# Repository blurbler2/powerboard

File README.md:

# Powerboard v1

A small 3.3 V supply module for battery-powered microcontroller projects: 4x AA NiMH in,
regulated 3.3 V out, with an ultra-low quiescent current buck converter (TI TPS62842, 60 nA Iq),
a switchable battery-voltage divider for an MCU ADC, a jumper for current measurement and
test points. Breadboard format with two 1x04 pin headers 12.7 mm apart, like
[olmBoard](https://github.com/azerimaker/olmBoard) (which uses the TPS62840 from the same family).

| | |
|---|---|
| Input | 4x AA NiMH, 4.8 ... 5.6 V (converter accepts 1.8 ... 6.5 V) |
| Output | 3.3 V (set by R7 = 52.3 kΩ 1 %) |
| Output current | up to 750 mA (converter limit); F1 holds 500 mA from the battery, which is about 600 mA at 3.3 V even with nearly empty cells. SW1 carries no load current (see [SW1](#sw1-onoff-switch)) |
| Quiescent current | ON: 60 nA (TPS62842) + MOSFET leakage, the battery divider draws nothing while it is off. OFF: converter shut down, 25 nA typ. (datasheet max 300 nA) + leakage |
| Protection | 500 mA polyfuse F1, reverse-polarity Schottky diode D1 (SS14) |
| Board | 16.0 x 45.72 mm, 2 layers, 1.6 mm, KiCad 10 |

## Board overview

Top view, switch at the top edge:

```
     ON <-- SW1 --> OFF  (actuator sticks out over the edge)
   Q1 R3              D1        F1
   R1 Q2                        J1  (battery: + upper pin, - square pad)
   R2 R4   TP1 (+BATT)
   C17     C14 C15 C2
   TP3 (GND)    U1                  TOP
                L1 R7
  J3 ●  GND     C1 C16       +BAT  ● J2
     ●  ADC                   GND  ●
     ●  EN      JP1 [BUCK|3V3] GND  ●
     ●  3V3                   3V3  ●
                       TP2 (+3V3)
```

## Connecting it

### Battery (J1)

2-pin socket, 2.54 mm pitch, for the plug of a 4x AA holder.

| J1 pin | Silkscreen | Connect |
|--------|------------|---------|
| 1 | square pad | battery − (black) |
| 2 | `+` | battery + (red) |

D1 blocks a reversed battery, so a wrong plug does no harm (the board just stays off).

### Pin headers J2 / J3

Mounted from the bottom: plastic under the board, long pins down into the breadboard. Pin 1 is
on the switch side. The labels are printed next to the pins on both sides of the board.

| Pin | J3 (left, `SIG`) | J2 (right, `PWR`) |
|-----|------------------|-------------------|
| 1 | GND | +BATT (battery after F1 and D1, live even when SW1 is OFF) |
| 2 | ADC (battery voltage / 2, only while EN is high) | GND |
| 3 | EN (enable battery measurement, 3.3 V logic input) | GND |
| 4 | +3V3 | +3V3 |

+3V3 on J2.4 and J3.4 is the same rail, after the current jumper JP1. All GND pins are the same.
J3 `EN` only switches the battery divider; it has nothing to do with SW1.

### SW1 on/off switch

SW1 is a C&K **OS102011MA1Q**, a right-angle (side-actuated) SPDT slide switch, through-hole.
The footprint looks big because of its two large oval pads: they are the soldered legs of the metal
frame that hold the switch mechanically and carry no signal. The three small pads in the middle
are the contacts.

SW1 does not sit in the battery line. It drives the enable pin of the converter (net `BUCK_EN`):

| Slider position | Silkscreen | Contacts (C&K switch function) | Result |
|-----------------|------------|--------------------------------|--------|
| left | `ON` | middle pin to left pin (2-3) → EN = +BATT | converter runs, +3V3 on |
| right | `OFF` | middle pin to right pin (1-2) → EN = GND | converter shut down (25 nA typ.), +3V3 discharged to 0 V |

- The slide direction comes from the C&K OS series datasheet: position 1 connects pins 1-2,
  position 2 connects pins 2-3, i.e. the slider always connects the middle pin to the outer pin
  on its own side. The `ON` / `OFF` labels are printed at the matching ends of the switch.
- Only the enable pin's input current flows through SW1, so its 100 mA contact rating does not
  limit the output. The load current goes J1 → F1 → D1 → converter.
- When OFF, the battery stays connected to +BATT (J2.1, TP1) and to the converter input. Take the
  batteries out (or unplug J1) for long storage; the standby current is far below the
  self-discharge of NiMH cells anyway.

### Microcontroller, e.g. STM32WB Nucleo

| Powerboard | Nucleo |
|------------|--------|
| J3.1 GND | GND |
| J3.2 ADC | any ADC input pin (Arduino header A0 ... A5) |
| J3.3 EN | any free GPIO, push-pull output |
| J3.4 +3V3 | 3V3, **only** if the Nucleo is not powered over USB at the same time |

If the Nucleo runs from USB, connect only GND, ADC and EN; never tie two 3.3 V supplies together.

The TPS62842 needs 3 ... 40 µF *effective* capacitance on its output (datasheet, COUT). C1 gives
about 5 µF at 3.3 V; everything the load adds on +3V3 counts too, so keep the load's own
capacitance below about 30 µF.

## Measuring the battery voltage (EN / ADC)

R1/R2 (100 kΩ / 100 kΩ, 1 %) divide the battery voltage by two. Q1 (AO3401A, P-channel) switches the
divider on and off at the battery side, Q2 (AO3400A, N-channel) lets a 3.3 V GPIO drive Q1.

| EN | State | Current |
|----|-------|---------|
| high (3.3 V) | Q2 on → Q1 on → divider on, ADC = VBAT / 2 | ≈ 37 µA (28 µA divider, 5.6 µA R3, 3.3 µA R4) |
| low or open | R4 keeps Q2 off, R3 keeps Q1 off → divider off, ADC = 0 V | MOSFET leakage only (nA) |

One measurement (100 ms at 37 µA) costs about 4 µC, roughly 1 nA on average when measuring
once per hour. The divider is off while the MCU is in reset or the pin is floating, so it never drains the battery
by accident. While it is off the ADC pin sees 0 V, never more than the MCU supply.

Measurement sequence:

1. Set EN high.
2. Wait at least **65 ms** (100 ms is comfortable): C17 (150 nF) charges through R1 ∥ R2 = 50 kΩ, τ = 7.5 ms; 8.3 τ settle to 12-bit accuracy.
3. Read the ADC: V_ADC.
4. Set EN low (or switch the pin to input / analog).
5. VBAT = 2 × V_ADC. This is the voltage after D1; the battery itself is about 0.2 ... 0.4 V higher (SS14 forward drop at the actual load).

Example (STM32 HAL, pin names are placeholders):

```c
HAL_GPIO_WritePin(MEAS_EN_GPIO_Port, MEAS_EN_Pin, GPIO_PIN_SET);
HAL_Delay(100);                                   /* C17 settling, >= 65 ms */
HAL_ADC_Start(&hadc1);
HAL_ADC_PollForConversion(&hadc1, 10);
uint32_t raw = HAL_ADC_GetValue(&hadc1);
HAL_GPIO_WritePin(MEAS_EN_GPIO_Port, MEAS_EN_Pin, GPIO_PIN_RESET);
float vbat = 2.0f * raw * 3.3f / 4095.0f;         /* 12 bit, VREF = 3.3 V */
```

## Current measurement (JP1)

JP1 is a 2-pin header with a jumper cap between the converter output and the +3V3 rail.
It is **not** a power connector and has no GND pin.

| JP1 pin | Silkscreen | Net |
|---------|------------|-----|
| 1 (square pad) | `BUCK` | converter output (U1 / L1 / C1) |
| 2 | `3V3` | +3V3 rail (J2.4, J3.4, TP2) |

The labels are on the top side, under the two pins.

- Normal operation: jumper cap **on**.
- Measuring: pull the jumper cap and connect the multimeter in current mode:
  red probe (mA / µA input) on `BUCK`, black probe (COM) on `3V3`.
  The meter then shows everything drawn from +3V3 through the headers.
- Start in the mA range: a µA range has a large shunt resistance, so the start-up current of an
  MCU can drop the voltage too far and reset it. Switch to µA once the MCU sleeps.
- Not included in this reading: the converter's own 60 nA, the battery divider (only while EN is
  high) and the MOSFET drive. To measure the total battery current, put the meter in the battery lead.

## Test points

SMD pads, 1.5 mm, for probe tips or small clips.

| TP | Net | Where |
|----|-----|-------|
| TP1 | +BATT (battery after F1 and D1) | below D1, next to Q2 |
| TP2 | +3V3 (after JP1) | bottom edge, right of JP1 |
| TP3 | GND | left side, next to C15 / C2 |

Battery voltage: TP1 against TP3. Output voltage: TP2 against TP3.

## Ordering the PCB (JLCPCB)

Upload `powerboard-hw/powerboard-v1/fabrication/powerboard-v1-gerbers.zip` (Gerbers + Excellon drill).

| Option | Setting |
|--------|---------|
| Layers | 2 |
| Dimensions | 16 x 45.72 mm (detected from the outline) |
| Material / thickness | FR-4, 1.6 mm |
| Outer copper | 1 oz |
| Surface finish | HASL lead-free; ENIG if you want flatter pads for U1 |
| Via covering | Tented (the files tent all vias) |
| Mark on PCB | "Specify a location": the order number goes on the `JLCJLCJLCJLC` text on the bottom |
| Everything else | default |

The design stays inside JLCPCB's standard 2-layer capabilities: tracks ≥ 0.25 mm,
clearance ≥ 0.2 mm, smallest hole 0.3 mm with a 0.6 mm via pad, copper-to-edge 0.5 mm,
silkscreen text 0.8 mm high with 0.15 mm stroke. This is a bare-PCB order; the parts come from
`bom/powerboard-v1-bom.csv` (JLCPCB assembly would additionally need LCSC part numbers).

## Assembly and first power-up

Hand-solder footprints throughout, except U1:

- **U1 (TPS62842, HVSSOP-8)** has an exposed pad underneath that must be soldered to GND. Use solder
  paste and hot air or a hot plate. With an iron only, you can feed solder into the pad from the
  bottom through its two vias, but that is fiddly. Solder U1 first, then the SMD parts, THT parts last.
- **L1** 2.2 µH, 1008 (2520) size; **C1** 10 µF X5R/X7R ≥ 10 V; **C2** 4.7 µF ≥ 10 V; **C14** 22 µF ≥ 16 V.
- **J2/J3** from the bottom (plastic under the board), **JP1, J1** from the top.

First power-up, without a load:

1. Check with an ohmmeter: TP1–TP3 and TP2–TP3 are not shorted.
2. SW1 to `OFF` (slider right), jumper cap on JP1, batteries in.
3. TP1–TP3 ≈ battery voltage minus 0.3 V, TP2–TP3 = 0 V.
4. SW1 to `ON` (slider left): TP2–TP3 = 3.3 V.
5. EN to 3.3 V: J3 ADC ≈ half of TP1 within 0.1 s; EN open: ADC = 0 V.

## Layout notes

- Signals on F.Cu, B.Cu is a solid GND plane, GND fill on F.Cu, stitching vias
- Converter laid out after the TPS62840 datasheet (DGR layout, fig. 63): C2 (4.7 µF) directly on
  VIN/EN and GND, MODE and pin 8 into the exposed pad with two thermal vias, VOS as a separate
  sense line to C1 away from the switching node, R7 on the VSET side away from SW
- Net classes: `Default` 0.4 mm, `Versorgung` (supply) 0.6 mm; copper-to-edge 0.5 mm
- Checks: ERC 0 errors / 0 warnings, DRC 0 violations, 0 unconnected, schematic parity OK

## Files

```
powerboard/
├── README.md
├── powerboard-docs/            renders: 3D, top, bottom, layout, schematic
└── powerboard-hw/
    ├── powerboard-lib/         project library: TPS62842DGRR symbol, DGR footprint, STEP model
    └── powerboard-v1/          KiCad 10 project
        ├── powerboard-v1.kicad_pro / .kicad_sch / .kicad_pcb / .kicad_dru
        ├── sym-lib-table, fp-lib-table   (only ${KIPRJMOD}-relative paths)
        ├── schematic/          schematic PDF
        ├── bom/                BOM (CSV, grouped by value and footprint)
        └── fabrication/        Gerbers, Excellon drill, position file, gerber zip
```

Only the KiCad standard libraries are needed besides this folder.

## Regenerating the outputs

From `powerboard-hw/powerboard-v1/`:

```bash
kicad-cli pcb export gerbers -l F.Cu,B.Cu,F.Paste,B.Paste,F.Silkscreen,B.Silkscreen,F.Mask,B.Mask,Edge.Cuts --use-drill-file-origin --subtract-soldermask -o fabrication/gerbers/ powerboard-v1.kicad_pcb
kicad-cli pcb export drill --drill-origin plot --excellon-separate-th --generate-map --map-format gerberx2 -o fabrication/gerbers/ powerboard-v1.kicad_pcb
kicad-cli pcb export pos --side both --format csv --units mm --use-drill-file-origin -o fabrication/powerboard-v1-pos.csv powerboard-v1.kicad_pcb
kicad-cli sch export bom --fields 'Reference,Value,Footprint,${QUANTITY},Datasheet,Description' --labels 'Refs,Value,Footprint,Qty,Datasheet,Description' --group-by 'Value,Footprint' -o bom/powerboard-v1-bom.csv powerboard-v1.kicad_sch
kicad-cli sch export pdf -o schematic/powerboard-v1.pdf powerboard-v1.kicad_sch
```

## Status

v1, not manufactured or tested yet.

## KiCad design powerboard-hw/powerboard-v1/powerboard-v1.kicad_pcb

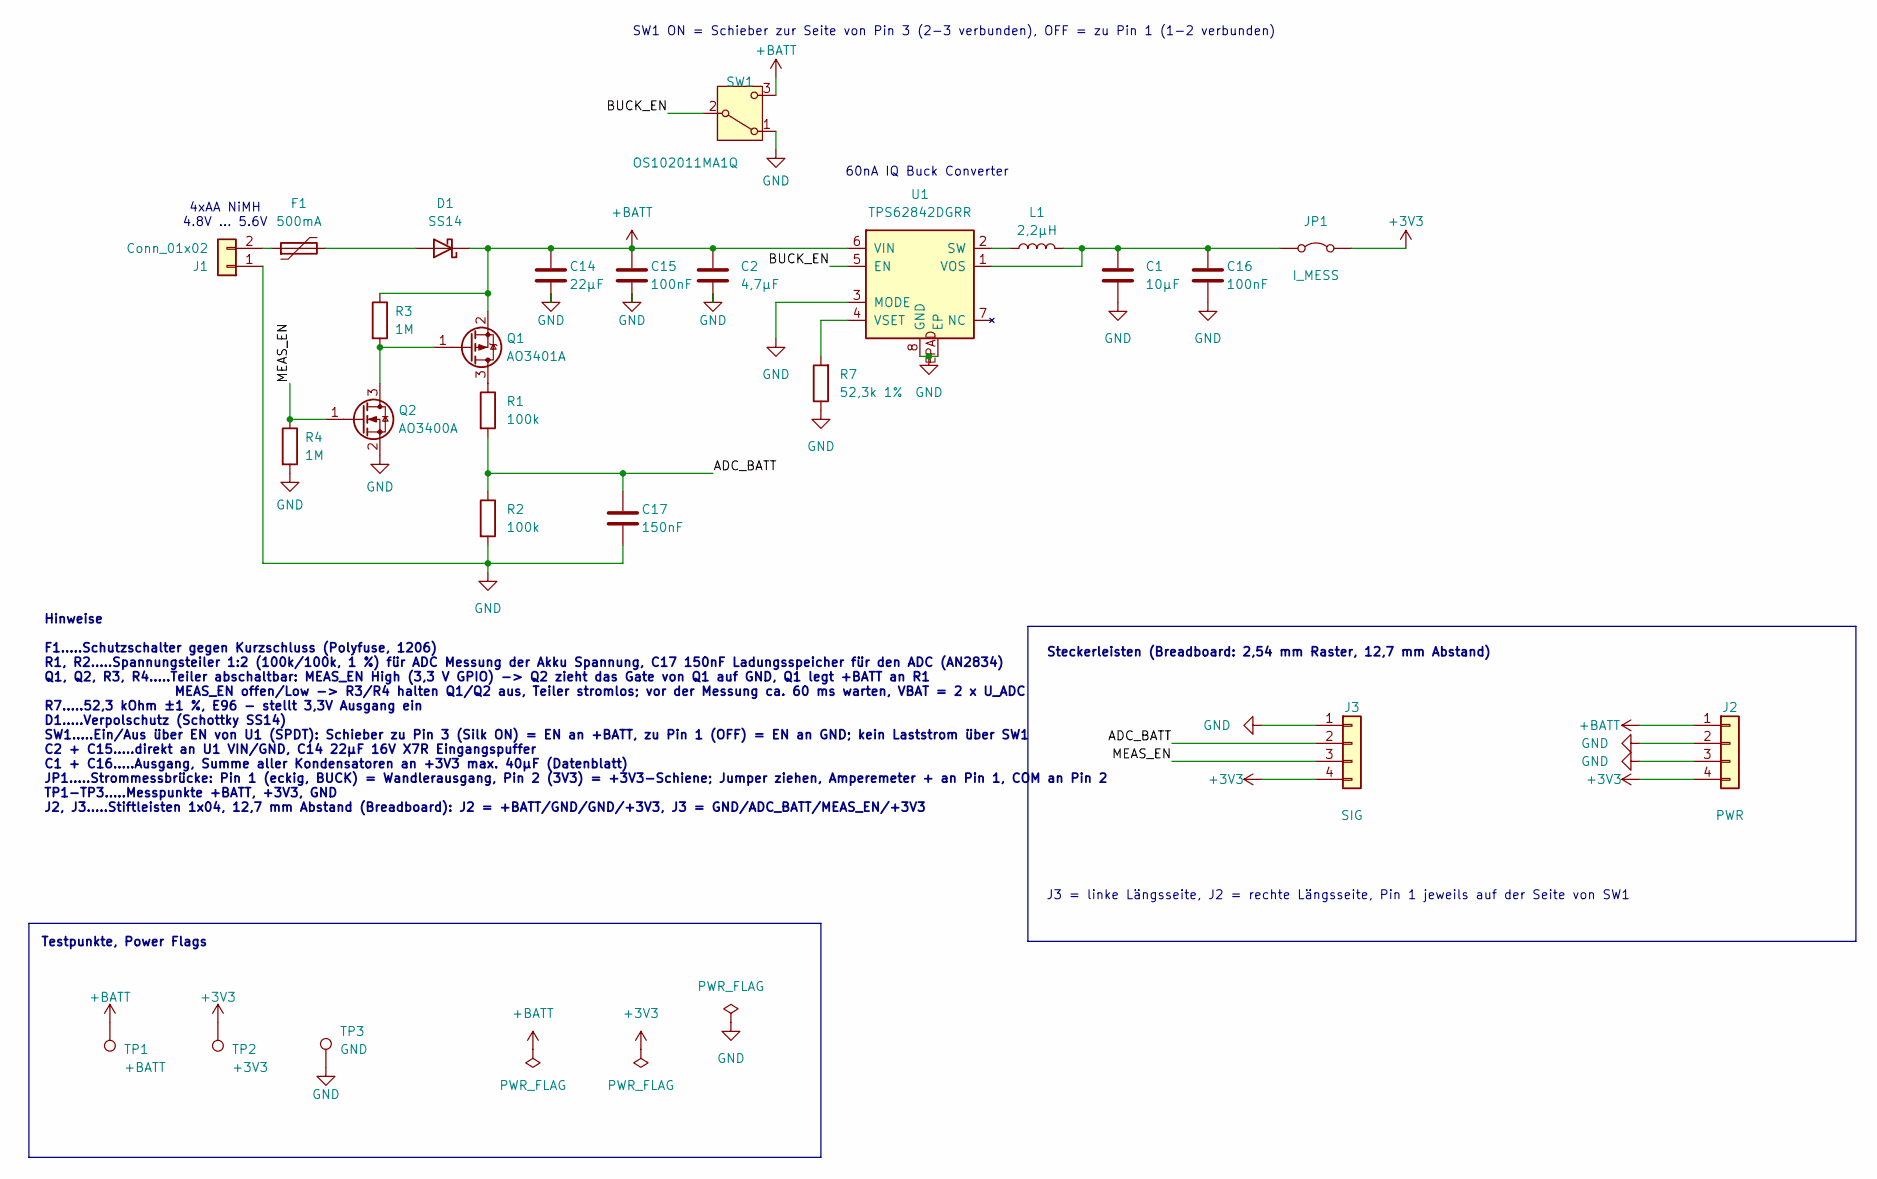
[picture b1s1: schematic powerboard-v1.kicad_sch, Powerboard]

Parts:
C1: 10µF; C_0805_2012Metric_Pad1.18x1.45mm_HandSolder
C2: 4,7µF; C_0805_2012Metric_Pad1.18x1.45mm_HandSolder
C14: 22µF; C_1206_3216Metric_Pad1.33x1.80mm_HandSolder
C15, C16: 100nF; C_0805_2012Metric_Pad1.18x1.45mm_HandSolder
C17: 150nF; C_0805_2012Metric_Pad1.18x1.45mm_HandSolder
D1: SS14; D_SMA
F1: 500mA; Fuse_1206_3216Metric_Pad1.42x1.75mm_HandSolder
J1: Conn_01x02; PinSocket_1x02_P2.54mm_Vertical
J2: PWR; PinHeader_1x04_P2.54mm_Vertical
J3: SIG; PinHeader_1x04_P2.54mm_Vertical
JP1: I_MESS; PinHeader_1x02_P2.54mm_Vertical
L1: 2,2µH; L_1008_2520Metric_Pad1.43x2.20mm_HandSolder
Q1: AO3401A; SOT-23
Q2: AO3400A; SOT-23
R1, R2: 100k; R_0805_2012Metric_Pad1.20x1.40mm_HandSolder
R3, R4: 1M; R_0805_2012Metric_Pad1.20x1.40mm_HandSolder
R7: 52,3k 1%; R_0805_2012Metric_Pad1.20x1.40mm_HandSolder
SW1: OS102011MA1Q; SW_Slide_SPDT_Angled_CK_OS102011MA1Q
TP1: +BATT; TestPoint_Pad_D1.5mm
TP2: +3V3; TestPoint_Pad_D1.5mm
TP3: GND; TestPoint_Pad_D1.5mm
U1: TPS62842DGRR; VSSOP_42DGRR_TEX-L

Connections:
+3V3: J2.4, J3.4, JP1.2 (B), TP2.1
+BATT: C2.1, C14.1, C15.1, D1.1 (K), J2.1, Q1.2 (S), R3.1, SW1.3 (C), TP1.1, U1.6 (VIN)
/ADC_BATT: C17.1, J3.2, R1.2, R2.1
/BUCK_EN: SW1.2 (B), U1.5 (EN)
/MEAS_EN: J3.3, Q2.1 (G), R4.1
GND: C1.1, C2.2, C14.2, C15.2, C16.2, C17.2, J1.1, J2.2, J2.3, J3.1, Q2.2 (S), R2.2, R4.2, R7.1, SW1.1 (A), TP3.1, U1.3 (MODE), U1.8 (GND), U1.EPAD (EP)
unnamed: D1.2 (A), F1.2
unnamed: F1.1, J1.2
unnamed: C1.2, C16.1, JP1.1 (A), L1.2, U1.1 (VOS)
unnamed: Q1.3 (D), R1.1
unnamed: Q1.1 (G), Q2.3 (D), R3.2
unnamed: L1.1, U1.2 (SW)
unnamed: R7.2, U1.4 (VSET)

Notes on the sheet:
60nA IQ Buck Converter
Testpunkte, Power Flags
Hinweise F1.....Schutzschalter gegen Kurzschluss (Polyfuse, 1206) R1, R2.....Spannungsteiler 1:2 (100k/100k, 1 %) für ADC Messung der Akku Spannung, C17 150nF Ladungsspeicher für den ADC (AN2834) Q1, Q2, R3, R4.....Teiler abschaltbar: MEAS_EN High (3,3 V GPIO) -> Q2 zieht das Gate von Q1 auf GND, Q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
4xAA NiMH 4.8V ... 5.6V
SW1 ON = Schieber zur Seite von Pin 3 (2-3 verbunden), OFF = zu Pin 1 (1-2 verbunden)
Steckerleisten (Breadboard: 2,54 mm Raster, 12,7 mm Abstand)
J3 = linke Längsseite, J2 = rechte Längsseite, Pin 1 jeweils auf der Seite von SW1

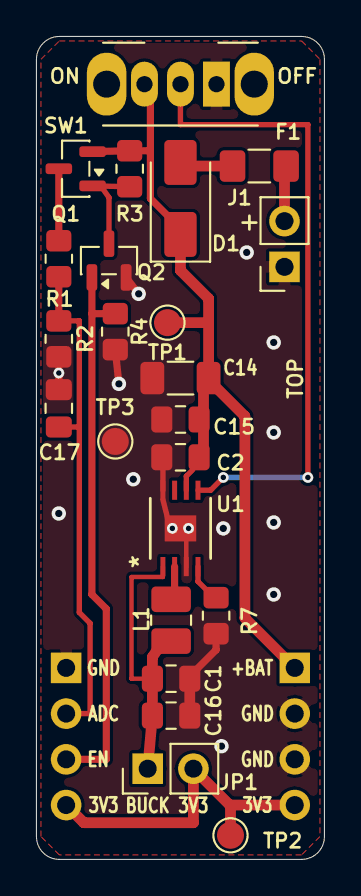
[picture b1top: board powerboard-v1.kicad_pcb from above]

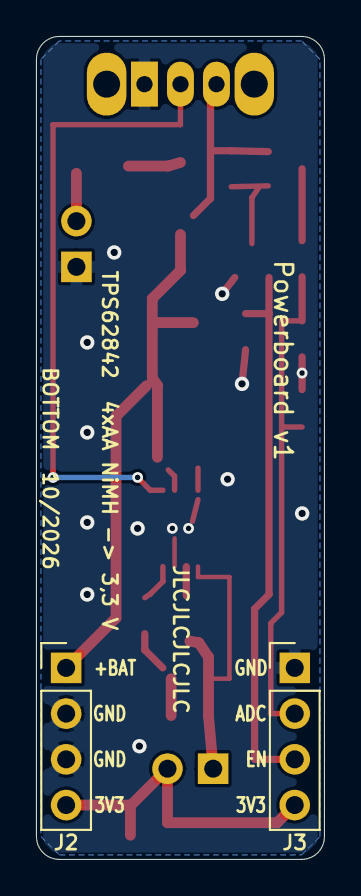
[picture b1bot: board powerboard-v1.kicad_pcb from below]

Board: 2 copper layers, 16.0 x 45.7 mm, 25 parts (2 on the bottom side), 13 nets.

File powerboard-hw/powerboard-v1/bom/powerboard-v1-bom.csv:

"Refs","Value","Footprint","Qty","Datasheet","Description"
"C1","10µF","Capacitor_SMD:C_0805_2012Metric_Pad1.18x1.45mm_HandSolder","1","","Unpolarized capacitor"
"C2","4,7µF","Capacitor_SMD:C_0805_2012Metric_Pad1.18x1.45mm_HandSolder","1","","Unpolarized capacitor"
"C14","22µF","Capacitor_SMD:C_1206_3216Metric_Pad1.33x1.80mm_HandSolder","1","","Unpolarized capacitor"
"C15,C16","100nF","Capacitor_SMD:C_0805_2012Metric_Pad1.18x1.45mm_HandSolder","2","","Unpolarized capacitor"
"C17","150nF","Capacitor_SMD:C_0805_2012Metric_Pad1.18x1.45mm_HandSolder","1","","Unpolarized capacitor"
"D1","SS14","Diode_SMD:D_SMA","1","https://www.vishay.com/docs/88746/ss12.pdf","40V 1A Schottky Barrier Rectifier Diode, SMA(DO-214AC)"
"F1","500mA","Fuse:Fuse_1206_3216Metric_Pad1.42x1.75mm_HandSolder","1","","Resettable fuse, polymeric positive temperature coefficient"
"J1","Conn_01x02","Connector_PinSocket_2.54mm:PinSocket_1x02_P2.54mm_Vertical","1","","Generic connector, single row, 01x02, script generated (kicad-library-utils/schlib/autogen/connector/)"
"J2","PWR","Connector_PinHeader_2.54mm:PinHeader_1x04_P2.54mm_Vertical","1","~","Generic connector, single row, 01x04, script generated (kicad-library-utils/schlib/autogen/connector/)"
"J3","SIG","Connector_PinHeader_2.54mm:PinHeader_1x04_P2.54mm_Vertical","1","~","Generic connector, single row, 01x04, script generated (kicad-library-utils/schlib/autogen/connector/)"
"JP1","I_MESS","Connector_PinHeader_2.54mm:PinHeader_1x02_P2.54mm_Vertical","1","","Jumper, 2-pole, closed/bridged"
"L1","2,2µH","Inductor_SMD:L_1008_2520Metric_Pad1.43x2.20mm_HandSolder","1","","Inductor"
"Q1","AO3401A","Package_TO_SOT_SMD:SOT-23","1","http://www.aosmd.com/pdfs/datasheet/AO3401A.pdf","-4.0A Id, -30V Vds, P-Channel MOSFET, SOT-23"
"Q2","AO3400A","Package_TO_SOT_SMD:SOT-23","1","http://www.aosmd.com/pdfs/datasheet/AO3400A.pdf","30V Vds, 5.7A Id, N-Channel MOSFET, SOT-23"
"R1,R2","100k","Resistor_SMD:R_0805_2012Metric_Pad1.20x1.40mm_HandSolder","2","","Resistor"
"R3,R4","1M","Resistor_SMD:R_0805_2012Metric_Pad1.20x1.40mm_HandSolder","2","~","Resistor"
"R7","52,3k 1%","Resistor_SMD:R_0805_2012Metric_Pad1.20x1.40mm_HandSolder","1","","Resistor"
"SW1","OS102011MA1Q","Button_Switch_THT:SW_Slide_SPDT_Angled_CK_OS102011MA1Q","1","~","Switch, single pole double throw"
"TP1","+BATT","TestPoint:TestPoint_Pad_D1.5mm","1","","test point"
"TP2","+3V3","TestPoint:TestPoint_Pad_D1.5mm","1","","test point"
"TP3","GND","TestPoint:TestPoint_Pad_D1.5mm","1","","test point"
"U1","TPS62842DGRR","powerboard:VSSOP_42DGRR_TEX-L","1","https://www.ti.com/lit/ds/symlink/tps62840.pdf","TPS6284x 750 mA step-down converter, 60 nA Iq, HVSSOP-8 (DGR). VOUT set by RSET on VSET (52.3k = 3.3 V); EN max 6.5 V; output capacitance 3-40 uF effective."
